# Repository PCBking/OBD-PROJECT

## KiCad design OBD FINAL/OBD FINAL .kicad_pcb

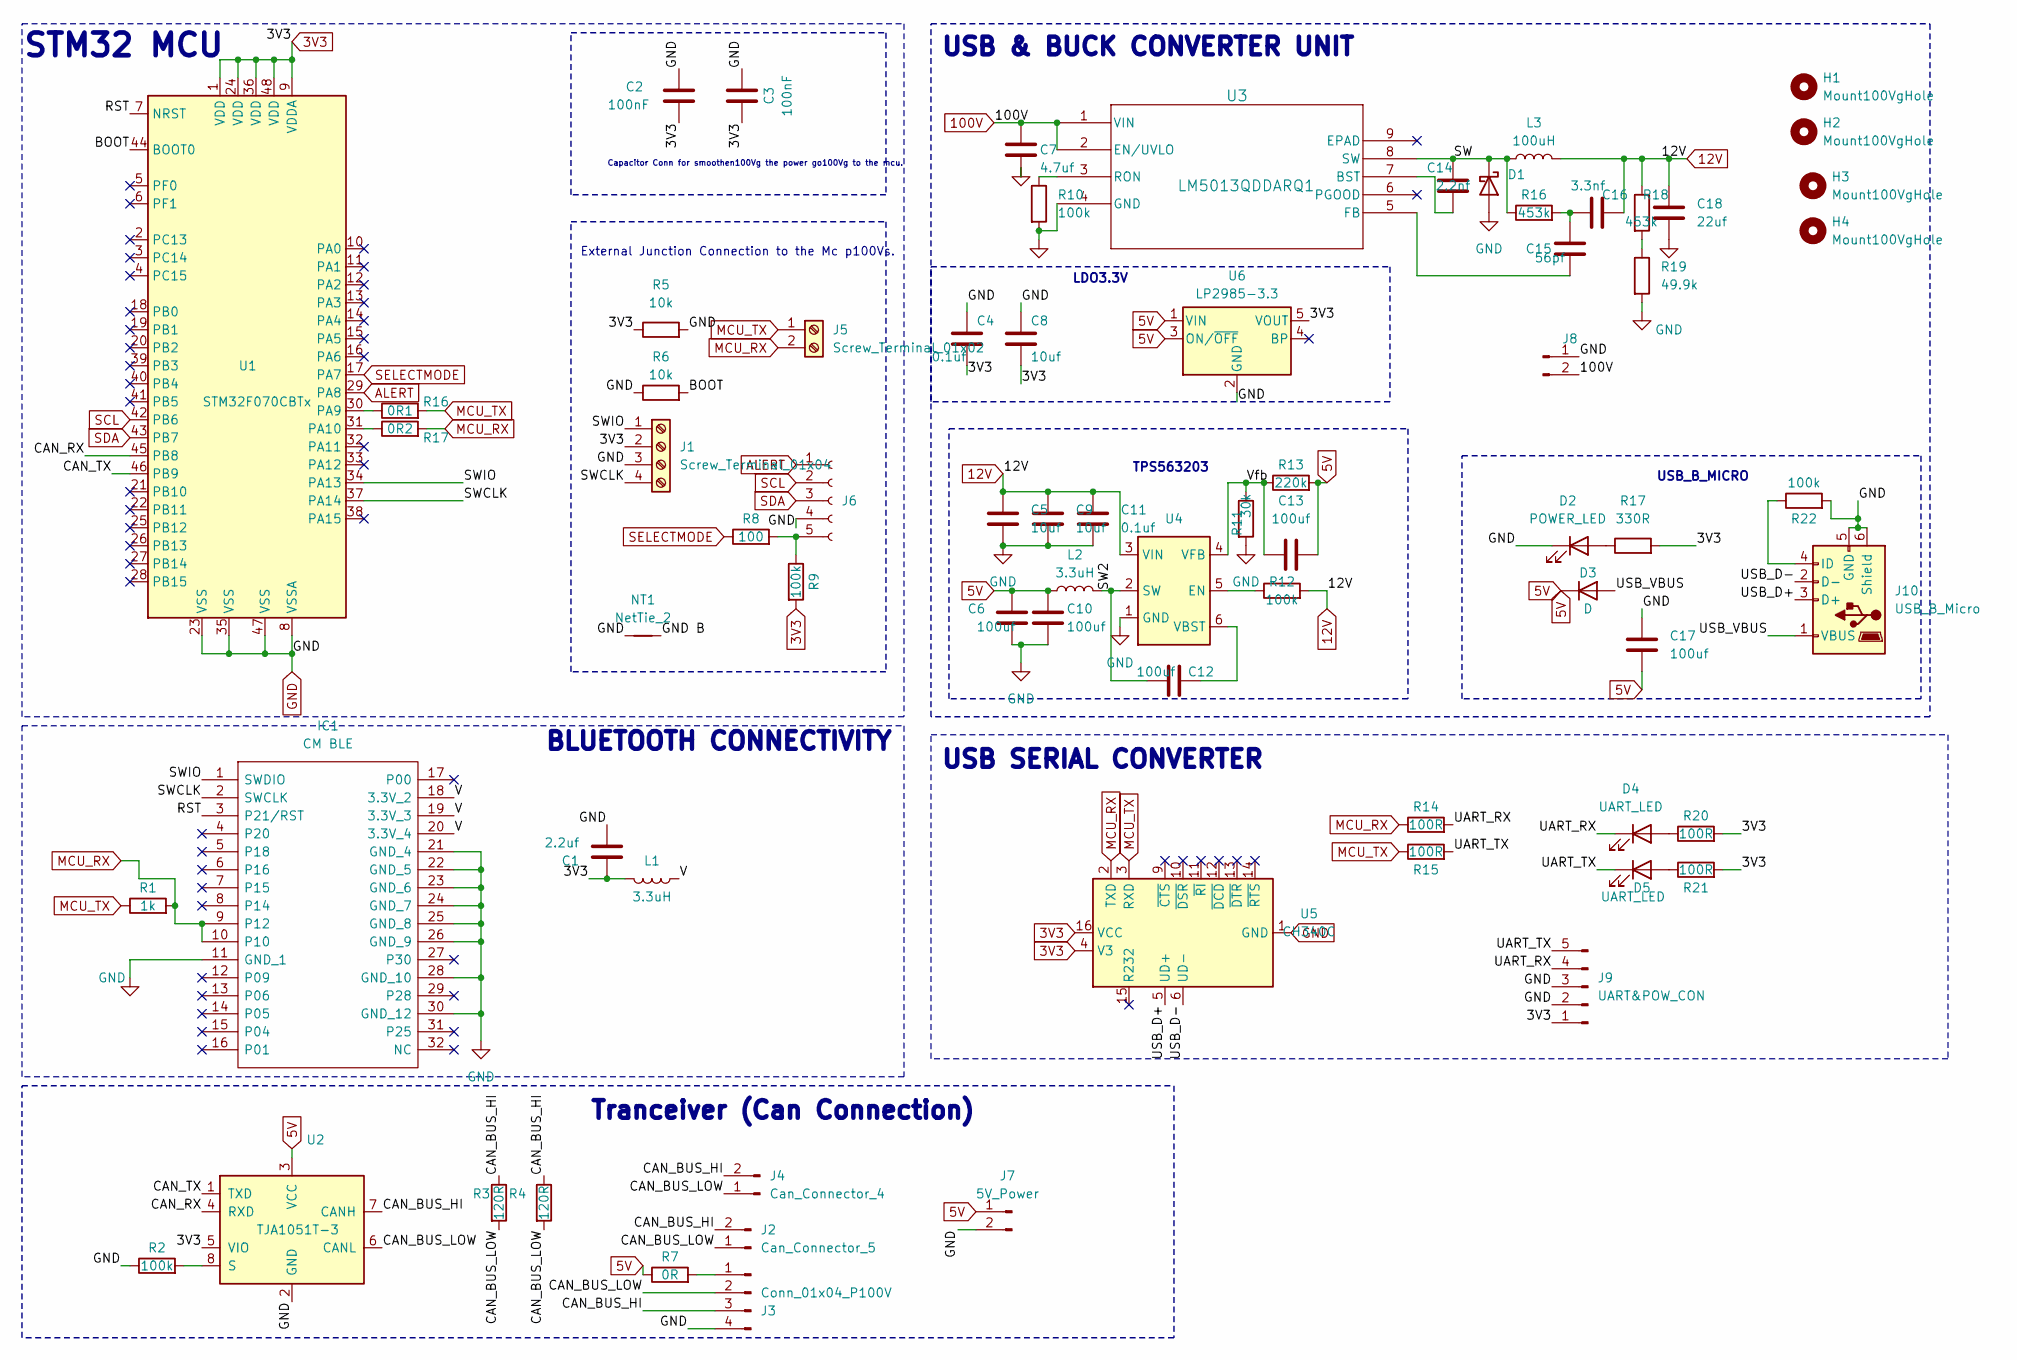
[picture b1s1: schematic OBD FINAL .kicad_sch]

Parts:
0R1: R16; R_0603_1608Metric_Pad0.98x0.95mm_HandSolder
0R2: R17; R_0603_1608Metric_Pad0.98x0.95mm_HandSolder
C1: 2.2uf; C_0603_1608Metric_Pad1.08x0.95mm_HandSolder
C2, C3: 100nF; C_1206_3216Metric_Pad1.33x1.80mm_HandSolder
C4, C11: 0.1uf; C_0603_1608Metric_Pad1.08x0.95mm_HandSolder
C5, C8, C9: 10uf; C_1210_3225Metric_Pad1.33x2.70mm_HandSolder
C6, C10, C12, C13, C17: 100uf; C_1206_3216Metric_Pad1.33x1.80mm_HandSolder
C7: 4.7uf; C_1210_3225Metric_Pad1.33x2.70mm_HandSolder
C14: 2.2nf; C_0603_1608Metric_Pad1.08x0.95mm_HandSolder
C15: 56pf; C_0603_1608Metric_Pad1.08x0.95mm_HandSolder
C16: 3.3nf; C_0805_2012Metric_Pad1.18x1.45mm_HandSolder
C18: 22uf; C_1206_3216Metric_Pad1.33x1.80mm_HandSolder
D1: D_Schottky; SMB_STM-M
D2: POWER_LED; CAPC1608X95
D3: D; D_0603_1608Metric_Pad1.05x0.95mm_HandSolder
D4, D5: UART_LED; CAPC1608X95
H1, H2, H3, H4: Mount100VgHole; MountingHole_2.7mm_M2.5_ISO7380_Pad_TopBottom
IC1: CM BLE; Manufacturer_Part_Number CBTMN10
J1: Screw_Terminal_01x04; TerminalBlock_bornier-4_P5.08mm
J2: Can_Connector_5; JST_EH_S2B-EH_1x02_P2.50mm_Horizontal
J3: Conn_01x04_P100V; JST_EH_S4B-EH_1x04_P2.50mm_Horizontal
J4: Can_Connector_4; JST_EH_S2B-EH_1x02_P2.50mm_Horizontal
J5: Screw_Terminal_01x02; TerminalBlock_bornier-2_P5.08mm
J6: Conn_01x05_Socket; JST_EH_S5B-EH_1x05_P2.50mm_Horizontal
J7: 5V_Power; JST_EH_S2B-EH_1x02_P2.50mm_Horizontal
J8: Conn_01x02_Pin; JST_EH_S2B-EH_1x02_P2.50mm_Horizontal
J9: UART&POW_CON; JST_EH_S5B-EH_1x05_P2.50mm_Horizontal
J10: USB_B_Micro; USB_Micro-B_Technik_TWP-4002D-H3
L1, L2: 3.3uH; INR33
L3: 100uH; 1267AY6R8NP3
NT1: NetTie_2; NetTie-2_SMD_Pad0.5mm
R1: 1k; R_0603_1608Metric_Pad0.98x0.95mm_HandSolder
R2, R9, R10, R12, R22: 100k; R_0603_1608Metric_Pad0.98x0.95mm_HandSolder
R3, R4: 120R; R_0603_1608Metric_Pad0.98x0.95mm_HandSolder
R5, R6: 10k; R_0603_1608Metric_Pad0.98x0.95mm_HandSolder
R7: 0R; R_0603_1608Metric_Pad0.98x0.95mm_HandSolder
R8: 100; R_0603_1608Metric_Pad0.98x0.95mm_HandSolder
R11: 30k; R_0603_1608Metric_Pad0.98x0.95mm_HandSolder
R13: 220k; R_0603_1608Metric_Pad0.98x0.95mm_HandSolder
R14, R15, R20, R21: 100R; R_0603_1608Metric_Pad0.98x0.95mm_HandSolder
R16, R18: 453k; R_0603_1608Metric_Pad0.98x0.95mm_HandSolder
R17: 330R; R_0603_1608Metric_Pad0.98x0.95mm_HandSolder
R19: 49.9k; R_0603_1608Metric_Pad0.98x0.95mm_HandSolder
U1: STM32F070CBTx; LQFP-48_7x7mm_P0.5mm
U2: TJA1051T-3; SOIC-8_3.9x4.9mm_P1.27mm
U3: LM5013QDDARQ1; Texas_HSOP-8-1EP_3.9x4.9mm_P1.27mm
U4: TPS563200; SOT-23-6
U5: CH340C; SOIC-16_3.9x9.9mm_P1.27mm
U6: LP2985-3.3; SOT-23-5

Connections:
3V3: C1.1, C2.1, C3.1, C4.2, C8.2, J1.2, J9.1, L1.2, R5.1, R9.2, R17.2, R20.2, R21.2, U1.1 (VDD), U1.9 (VDDA), U1.24 (VDD), U1.36 (VDD), U1.48 (VDD), U2.5 (VIO), U5.4 (V3), U5.16 (VCC), U6.5 (VOUT)
5V: C6.1, C10.1, C13.2, C17.2, D3.1 (K), J7.1, L2.1, R7.1, R13.2, U2.3 (VCC), U6.1 (VIN), U6.3 (ON/~OFF)
12V: C5.1, C9.1, C11.1, C16.2, C18.1, L3.2, R12.2, R18.1, U4.3 (VIN)
100V: C7.1, J8.2, U3.1 (VIN), U3.2 (EN/UVLO)
/BOOT: R6.2, U1.44 (BOOT0)
/CAN_BUS_HI: J2.2, J3.3, J4.2, R3.1, R4.1, U2.7 (CANH)
/CAN_BUS_LOW: J2.1, J3.2, J4.1, R3.2, R4.2, U2.6 (CANL)
/CAN_RX: U1.45 (PB8), U2.4 (RXD)
/CAN_TX: U1.46 (PB9), U2.1 (TXD)
/GND B: NT1.2
/RST: IC1.3 (P21/RST), U1.7 (NRST)
/SW: C14.1, D1.1 (K), L3.1, R16.1, U3.8 (SW)
/SW2: C12.1, L2.2, U4.2 (SW)
/SWCLK: IC1.2 (SWCLK), J1.4, U1.37 (PA14)
/SWIO: IC1.1 (SWDIO), J1.1, U1.34 (PA13)
/UART_RX: D4.1 (K), J9.4, R14.2
/UART_TX: D5.1 (K), J9.5, R15.2
/USB_D+: J10.3 (D+), U5.5 (UD+)
/USB_D-: J10.2 (D-), U5.6 (UD-)
/USB_VBUS: D3.2 (A), J10.1 (VBUS)
/V: IC1.18 (3.3V_2), IC1.19 (3.3V_3), IC1.20 (3.3V_4), L1.1
/Vfb: C13.1, R11.1, R13.1, U4.4 (VFB)
ALERT: J6.1, U1.29 (PA8)
GND: C1.2, C2.2, C3.2, C4.1, C5.2, C6.2, C7.2, C8.1, C9.2, C10.2, C11.2, C17.1, C18.2, D1.2 (A), D2.1 (K), IC1.11 (GND_1), IC1.21 (GND_4), IC1.22 (GND_5), IC1.23 (GND_6), IC1.24 (GND_7), IC1.25 (GND_8), IC1.26 (GND_9), IC1.28 (GND_10), IC1.30 (GND_12), J1.3, J3.4, J6.4, J7.2, J8.1, J9.2, J9.3, J10.5 (GND), J10.6 (Shield), NT1.1, R2.1, R5.2, R6.1, R10.2, R11.2, R19.2, R22.2, U1.8 (VSSA), U1.23 (VSS), U1.35 (VSS), U1.47 (VSS), U2.2 (GND), U3.4 (GND), U4.1 (GND), U5.1 (GND), U6.2 (GND)
MCU_RX: 0R2.2, IC1.9 (P12), IC1.10, J5.2, R1.2, R14.1, U5.2 (TXD)
MCU_TX: 0R1.2, J5.1, R1.1, R15.1, U5.3 (RXD)
unnamed: C15.1, C16.1, R16.2
unnamed: D2.2 (A), R17.1
unnamed: D4.2 (A), R20.1
unnamed: D5.2 (A), R21.1
unnamed: J3.1, R7.2
unnamed: J6.5, R8.2, R9.1
unnamed: J10.4 (ID), R22.1
unnamed: R18.2, R19.1
unnamed: 0R1.1, U1.30 (PA9)
unnamed: 0R2.1, U1.31 (PA10)
unnamed: R2.2, U2.8 (S)
unnamed: C14.2, U3.7 (BST)
unnamed: C15.2, U3.5 (FB)
unnamed: R10.1, U3.3 (RON)
unnamed: R12.1, U4.5 (EN)
unnamed: C12.2, U4.6 (VBST)
SCL: J6.2, U1.42 (PB6)
SDA: J6.3, U1.43 (PB7)
SELECTMODE: R8.1, U1.17 (PA7)

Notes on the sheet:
Capacitor Conn for smoothen100Vg the power go100Vg to the mcu.
TPS563203
BLUETOOTH CONNECTIVITY
USB SERIAL CONVERTER
Tranceiver (Can Connection)
USB_B_MICRO
External Junction Connection to the Mc p100Vs.
USB & BUCK CONVERTER UNIT
STM32 MCU
LDO3.3V

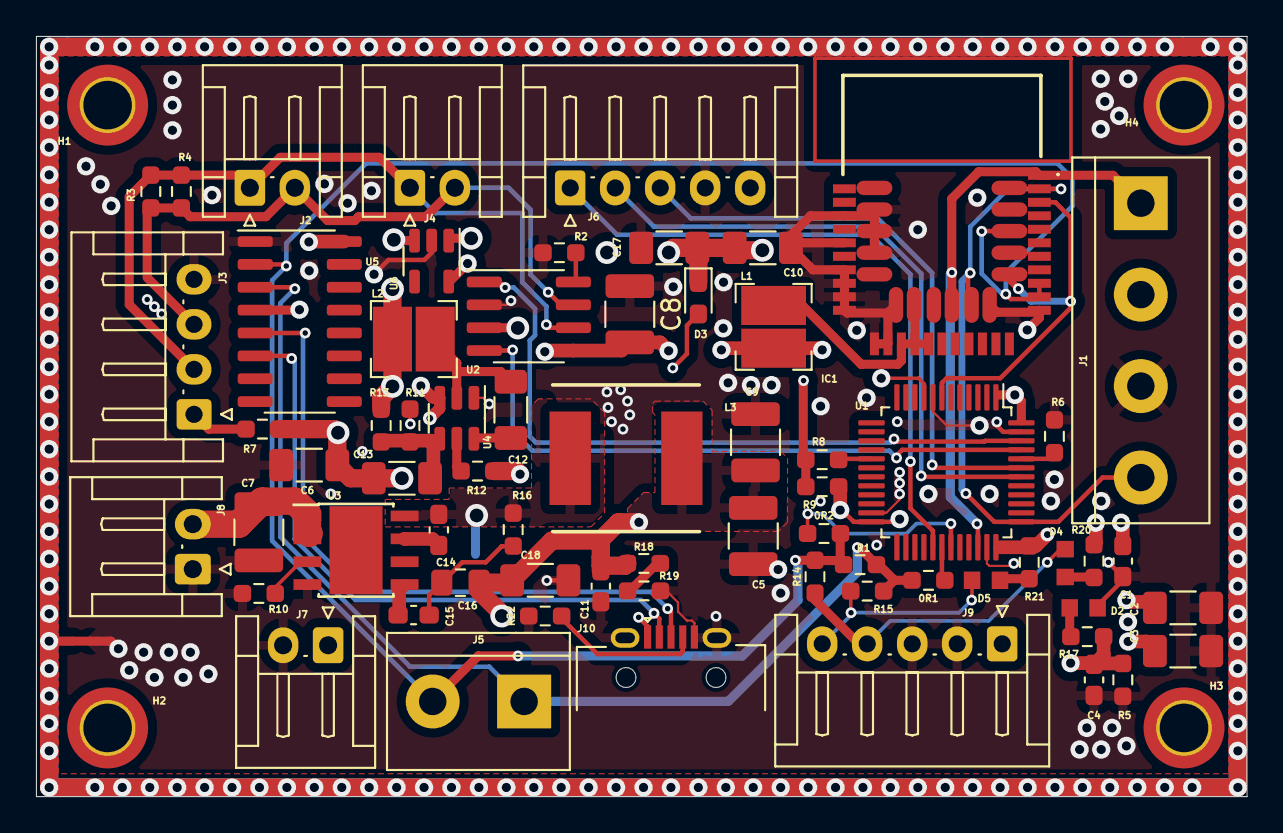
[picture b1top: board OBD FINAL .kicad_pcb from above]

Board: 4 copper layers, 67.3 x 42.2 mm, 72 parts (1 on the bottom side), 44 nets.
